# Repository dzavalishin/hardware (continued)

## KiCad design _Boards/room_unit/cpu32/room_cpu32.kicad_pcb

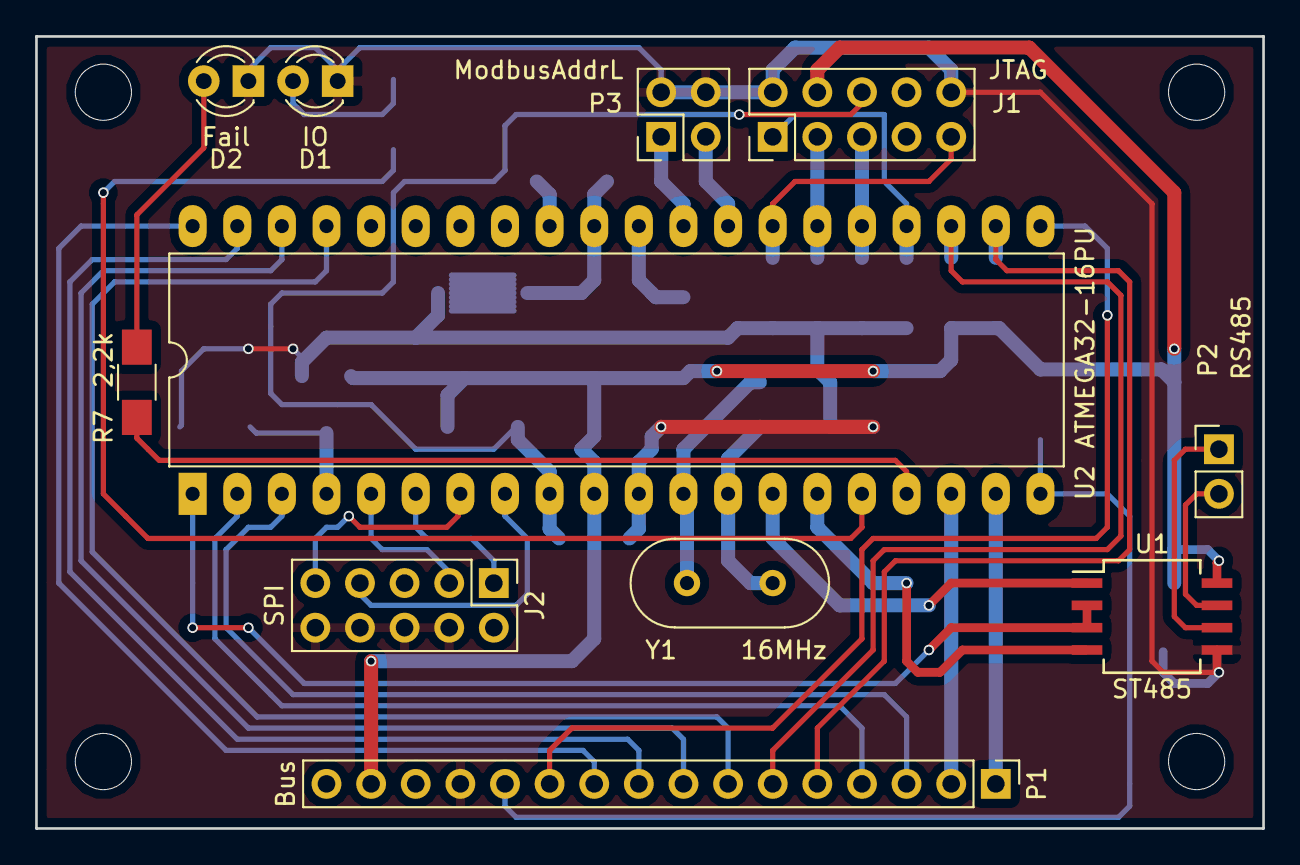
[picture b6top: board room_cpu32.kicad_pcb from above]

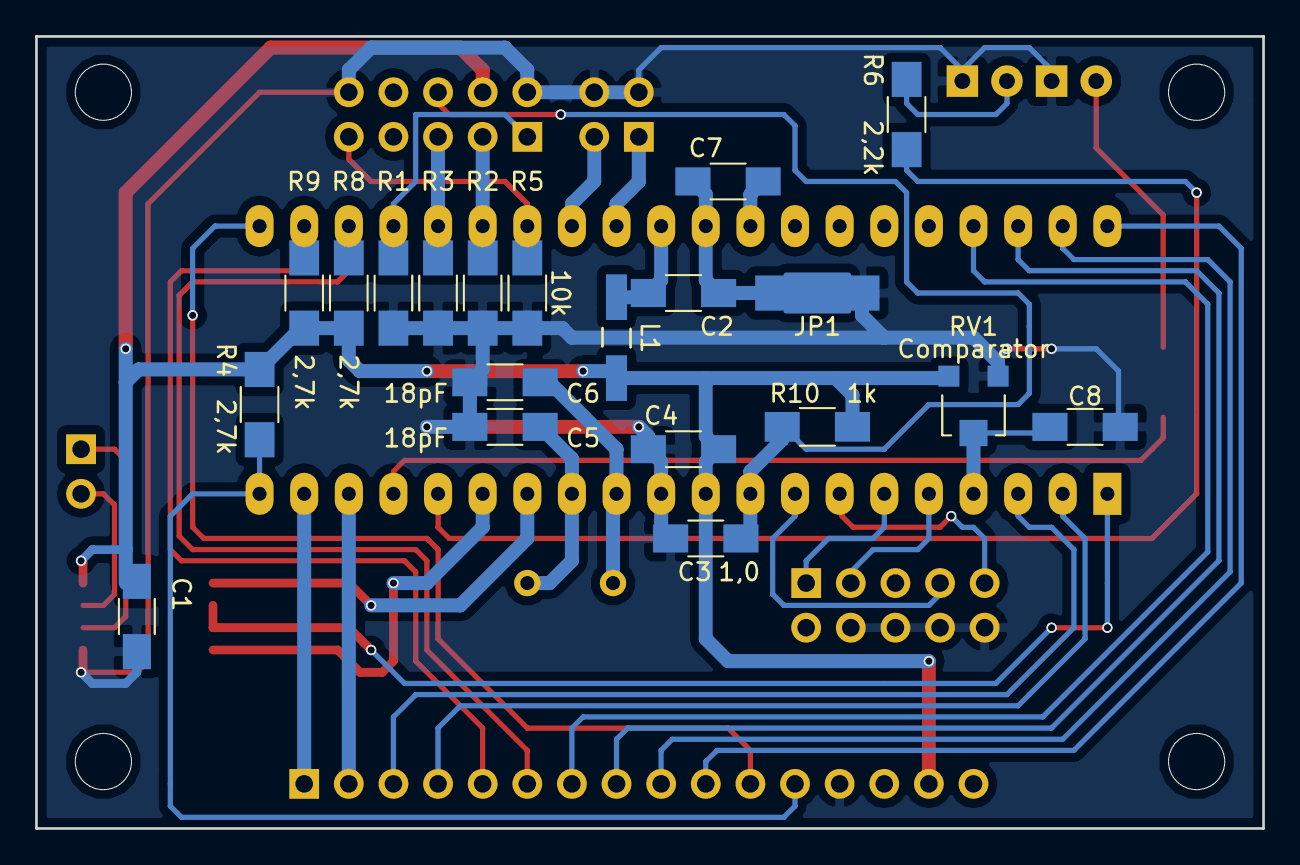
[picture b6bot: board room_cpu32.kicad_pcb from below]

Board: 2 copper layers, 69.8 x 45.1 mm, 31 parts (20 on the bottom side), 40 nets.

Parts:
C1, C2, C4, C8: 0,1; C_1206_HandSoldering
C3, C7: 1,0; C_1206_HandSoldering
C5, C6: 18pF; C_1206_HandSoldering
D1: IO; LED_D3.0mm
D2: Fail; LED_D3.0mm
J1: JTAG; Pin_Header_Straight_2x05_Pitch2.54mm
J2: SPI; Pin_Header_Straight_2x05_Pitch2.54mm
JP1: Jumper; NetTie-I_Connected_SMD
L1: 120uH; Choke_SMD_1206_Handsoldering
P1: Bus; Pin_Header_Straight_1x16_Pitch2.54mm
P2: RS485; Pin_Header_Straight_1x02_Pitch2.54mm
P3: ModbusAddrL; Pin_Header_Straight_2x02_Pitch2.54mm
R1, R2, R3, R5: 10k; R_1206_HandSoldering
R4, R8, R9: 2,7k; R_1206_HandSoldering
R6, R7: 2,2k; R_1206_HandSoldering
R10: 1k; R_1206_HandSoldering
RV1: Comparator; Potentiometer_Trimmer-EVM3E
U1: ST485; SO-8_5.3x6.2mm_Pitch1.27mm
U2: ATMEGA32-16PU; DIP-40_W15.24mm_LongPads
Y1: 16MHz; Crystal_HC49-U_Vertical

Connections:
+5V: C1.2, C4.2, J1.4, L1.2, P1.15, R4.2, R8.2, R9.2, R10.1, RV1.3, U1.8, U2.10
/1Wire: P1.12, R4.1, U2.20
/AI0: P1.10, U2.40
/AI1: P1.9, U2.39
/AI2: P1.8, U2.38
/AI3: P1.7, U2.37
/DI0: P1.4, U2.2
/DI1: P1.3, U2.3
/DO0: P1.2, U2.18
/DO1: P1.1, U2.19
/DO2: P1.11, U2.21
/Fail_Led: R7.2, U2.17
/IO_Led: R6.2, U2.16
/JTAG_TCK: J1.1, R1.1, U2.24
/JTAG_TDI: J1.9, R5.1, U2.27
/JTAG_TDO: J1.3, R2.1, U2.26
/JTAG_TMS: J1.5, R3.1, U2.25
/MISO: J2.9, U2.7
/MOSI: J2.1, U2.6
/Rx: U1.1, U2.14
/SCK: J2.7, U2.8
/SCL: P1.5, R9.1, U2.22
/SDA: P1.6, R8.1, U2.23
/Tx: U1.4, U2.15
/TxE: U1.2, U1.3, U2.1
/~RST: C3.1, J1.6, R10.2, U2.9
/~SS: J2.3, U2.5
GND: C1.1, C3.2, C4.1, C5.2, C6.2, C8.2, D1.1, D2.1, J1.2, J1.10, J2.4, J2.6, J2.8, J2.10, JP1.1, P1.13, P3.2, P3.4, R1.2, R2.2, R3.2, R5.2, RV1.1, U1.5, U2.11
GNDA: C2.2, C7.2, JP1.2, U2.31
unnamed: C2.1, L1.1, U2.30
unnamed: C5.1, U2.13, Y1.1
unnamed: C6.1, U2.12, Y1.2
unnamed: C7.1, U2.32
unnamed: C8.1, RV1.2, U2.4
unnamed: D1.2, R6.1
unnamed: D2.2, R7.1
unnamed: P2.1, U1.6
unnamed: P2.2, U1.7
unnamed: P3.1, U2.29
unnamed: P3.3, U2.28
